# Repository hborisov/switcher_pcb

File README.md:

# Switcher – A WiFi Open Source Power Switch and Socket

[Detailed description](http://hristoborisov.com/index.php/projects/switcher-a-wifi-open-source-power-switch/)
</img>
</img>

<a href="https://oshpark.com/shared_projects/eMwHjMz0"></img></a>

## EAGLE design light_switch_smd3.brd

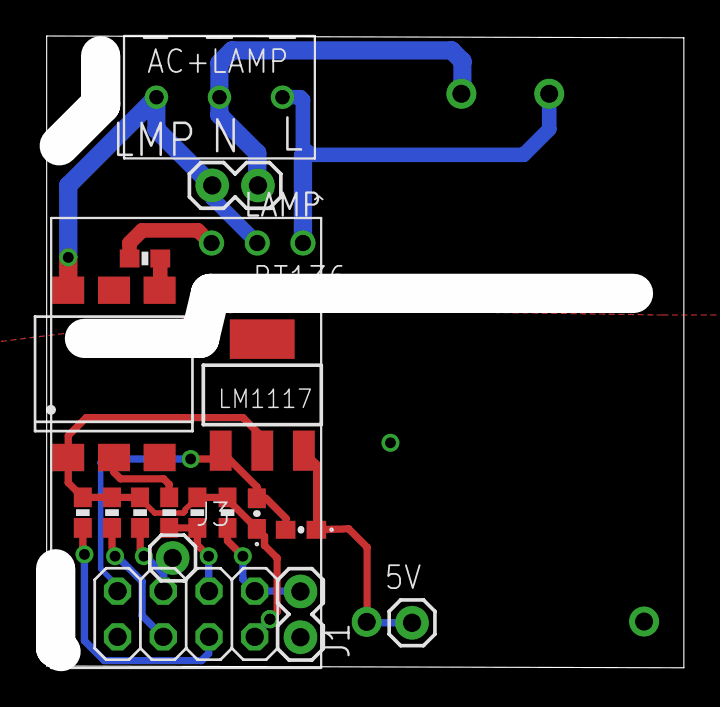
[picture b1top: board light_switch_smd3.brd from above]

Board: 2 copper layers, 35.4 x 35.1 mm, 19 parts (1 on the bottom side), 14 nets.

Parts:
5V: 1X01
AC+LAMP: DG350-3.5-03P
BT136: BT136; BT136-PKG
C1, C2: 10uF; 0603-POL
J1: 1X02
J3: 1X01
LAMP: 1X02
LM1117: LM1117; SOT223
OK1: MOC3033S; DIL6-SMD
R1, R2, R3, R4, R5: 3.3K; 0603-RES
R6: 430; 0603-RES
R7: 470; 0603-RES
U$1: HI-LINK5V-ACDC; AC5V
U$2: ESP8266-01

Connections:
GND: C1.K, C2.K, J1.1, LM1117.1, U$1.5V_GND, U$2.8
unnamed: J1.2, R3.2, U$2.2
unnamed: R2.1, U$2.5
unnamed: C1.A, LM1117.2, OK1.1, R1.1, R2.2, R3.1, R4.1, R5.2, U$2.1
unnamed: OK1.2, R6.2
unnamed: BT136.G, R7.2
unnamed: OK1.4, R7.1
unnamed: AC+LAMP.P$1, BT136.T2, LAMP.1, OK1.6
unnamed: R4.2, R6.1, U$2.4
unnamed: AC+LAMP.P$2, LAMP.2, U$1.AC2
unnamed: AC+LAMP.P$3, BT136.T1, U$1.AC1
unnamed: 5V.1, C2.A, LM1117.3, U$1.5V_VCC
unnamed: J3.1, R5.1, U$2.6
unnamed: R1.2, U$2.3

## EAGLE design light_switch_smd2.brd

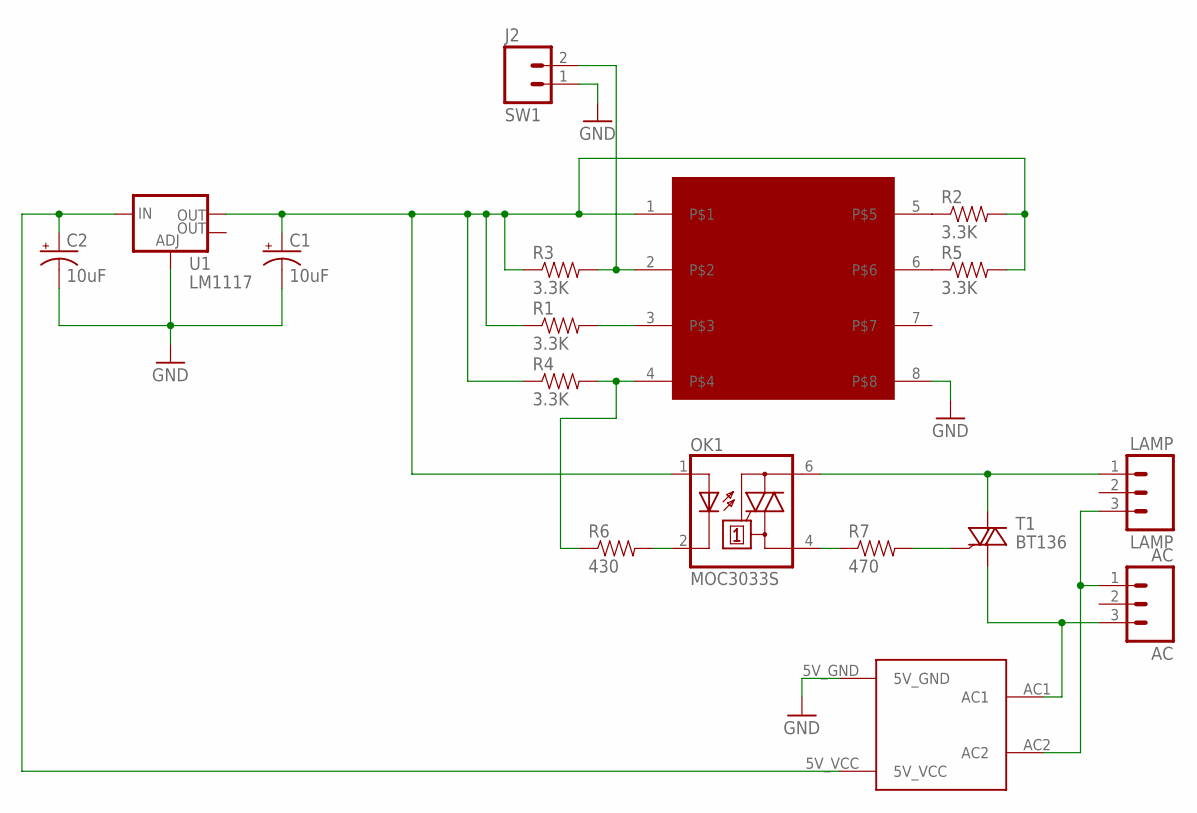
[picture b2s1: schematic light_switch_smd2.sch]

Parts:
AC: AC; 1X03_NO_SILK
C1, C2: 10uF; EIA3216
J2: SW1; 1X02_LONGPADS
LAMP: LAMP; 1X03_NO_SILK
OK1: MOC3033S; DIL6-SMD
R1, R2, R3, R4, R5: 3.3K; 1206
R6: 430; 1206
R7: 470; 1206
T1: BT136; TO220AB
U1: LM1117; SOT223
U$1: HI-LINK5V-ACDC; AC5V
U$2: ESP8266-01

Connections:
GND: C1.C (-), C2.C (-), J2.1, U1.1 (ADJ), U$1.5V_GND, U$2.8
unnamed: J2.2, R3.2, U$2.2
unnamed: R2.1, U$2.5
unnamed: C1.A (+), OK1.1 (A), R1.1, R2.2, R3.1, R4.1, R5.2, U1.2 (OUT), U$2.1
unnamed: R1.2, U$2.3
unnamed: OK1.2 (C), R6.2
unnamed: R7.2, T1.3 (G)
unnamed: OK1.4 (A1), R7.1
unnamed: LAMP.1, OK1.6 (A2), T1.2 (A2)
unnamed: R4.2, R6.1, U$2.4
unnamed: AC.1, LAMP.3, U$1.AC2
unnamed: AC.3, T1.1 (A1), U$1.AC1
unnamed: C2.A (+), U1.3 (IN), U$1.5V_VCC
unnamed: R5.1, U$2.6

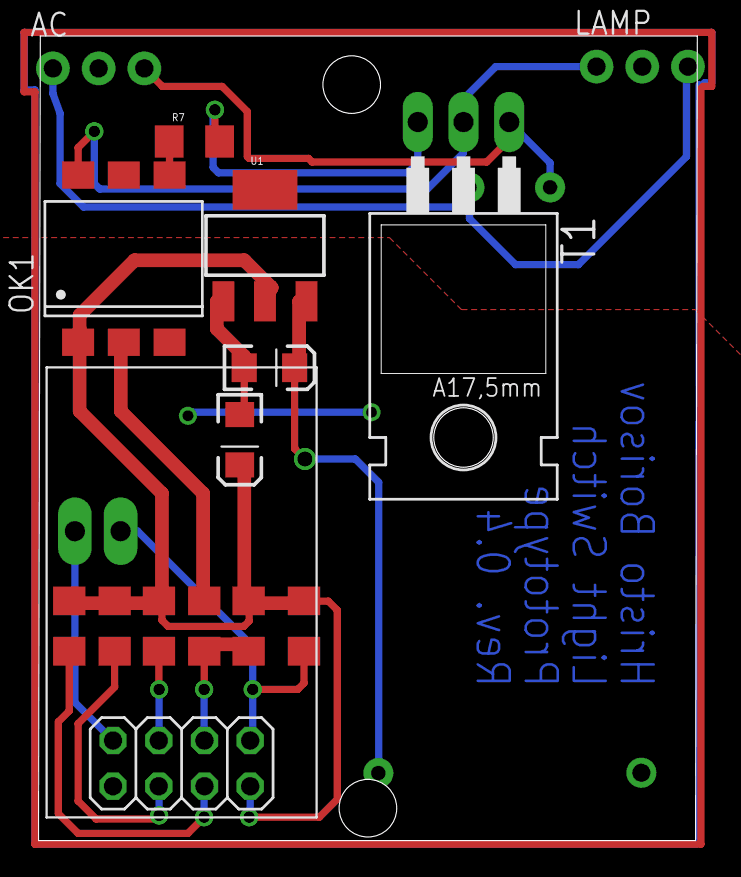
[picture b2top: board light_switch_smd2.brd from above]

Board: 2 copper layers, 36.6 x 44.7 mm, 17 parts (1 on the bottom side), 14 nets.

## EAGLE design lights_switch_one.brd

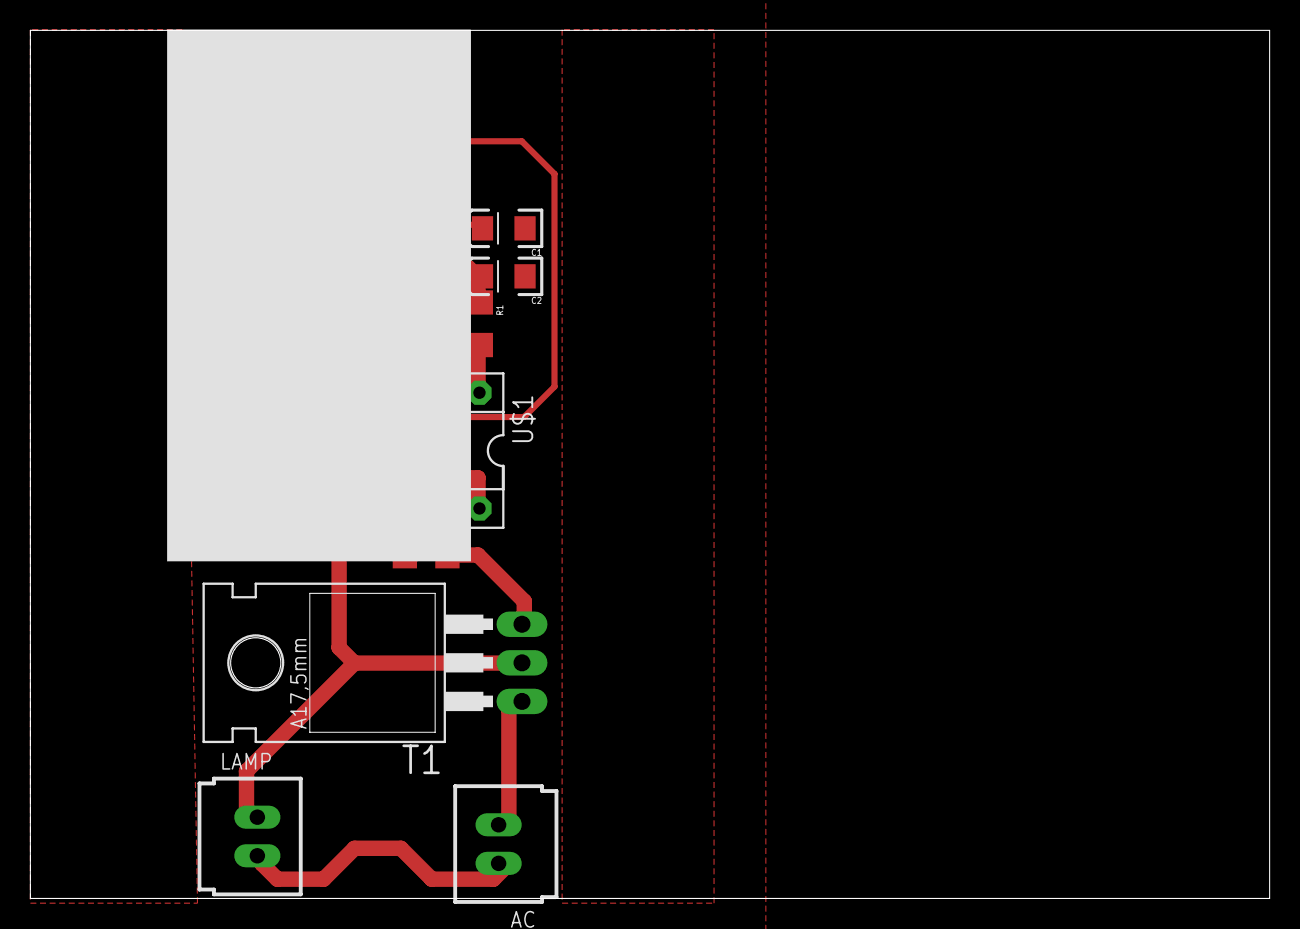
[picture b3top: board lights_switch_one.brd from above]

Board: 2 copper layers, 81.6 x 57.1 mm, 16 parts (1 on the bottom side), 14 nets.

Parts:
AC: C-GRID-02-70543; 70543-02
C1, C2: EIA3216
E$1: AC5V
ESP8266: 2X4
LAMP: C-GRID-02-70543; 70543-02
R1, R2, R3, R4, R5, R6, R7: 1206
T1: BT136; TO220AB
U1: SOT223
U$1: MOC3031-M; DIL06

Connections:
GND: C1.C, C2.C, ESP8266.8, U1.1
unnamed: ESP8266.3, R3.2
unnamed: ESP8266.5, R4.2
unnamed: ESP8266.2, R2.1
unnamed: ESP8266.4, R5.1, U$1.2
unnamed: ESP8266.6, R6.1
unnamed: R1.2, U$1.1
unnamed: R7.1, U$1.4
unnamed: R7.2, T1.3
unnamed: AC.2, T1.1
unnamed: AC.1, LAMP.2
unnamed: LAMP.1, T1.2, U$1.6
unnamed: C2.A, ESP8266.1, R1.1, R2.2, R3.1, R4.1, R5.2, R6.2, U1.2, U1.4
VCC: C1.A, U1.3

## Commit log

2016-09-03 Addign milling information
2016-09-03 Rev 0.8 - pcb shrinked a bit.
2016-09-03 Changing the BT136 device
2016-09-03 Removing files from index
2016-09-03 version 3, several correction added
2016-09-03 Adding labels to the power outlet
2016-09-03 v.2 Final - 2
2016-09-03 adding output files
2016-09-03 Version 4 revised and ready.
2016-09-03 pcb v4: distance between power supply pins corrected.\nSeveral vias added.
2016-09-03 light switch version 6 minor adjustments
2016-09-03 Adding one more milling cut
2016-09-03 v.2 Final
2016-09-03 More minor corrections.
2016-09-03 Deleting some files
2016-09-03 Version 5 ready and works. Minor correction on the triac placement
2016-09-03 Changing gitignore
2016-09-03 Rev. 0.7 - Light Switch is minified and the silkscreen is cleared
2016-09-03 Removing some files from the repository
2016-11-18 Fixing erroneous ground planes

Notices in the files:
parts and their libraries:
SparkFun-Capacitors: Licensing: Creative Commons ShareAlike 4.0 International - https://creativecommons.org/licenses/by-sa/4.0
